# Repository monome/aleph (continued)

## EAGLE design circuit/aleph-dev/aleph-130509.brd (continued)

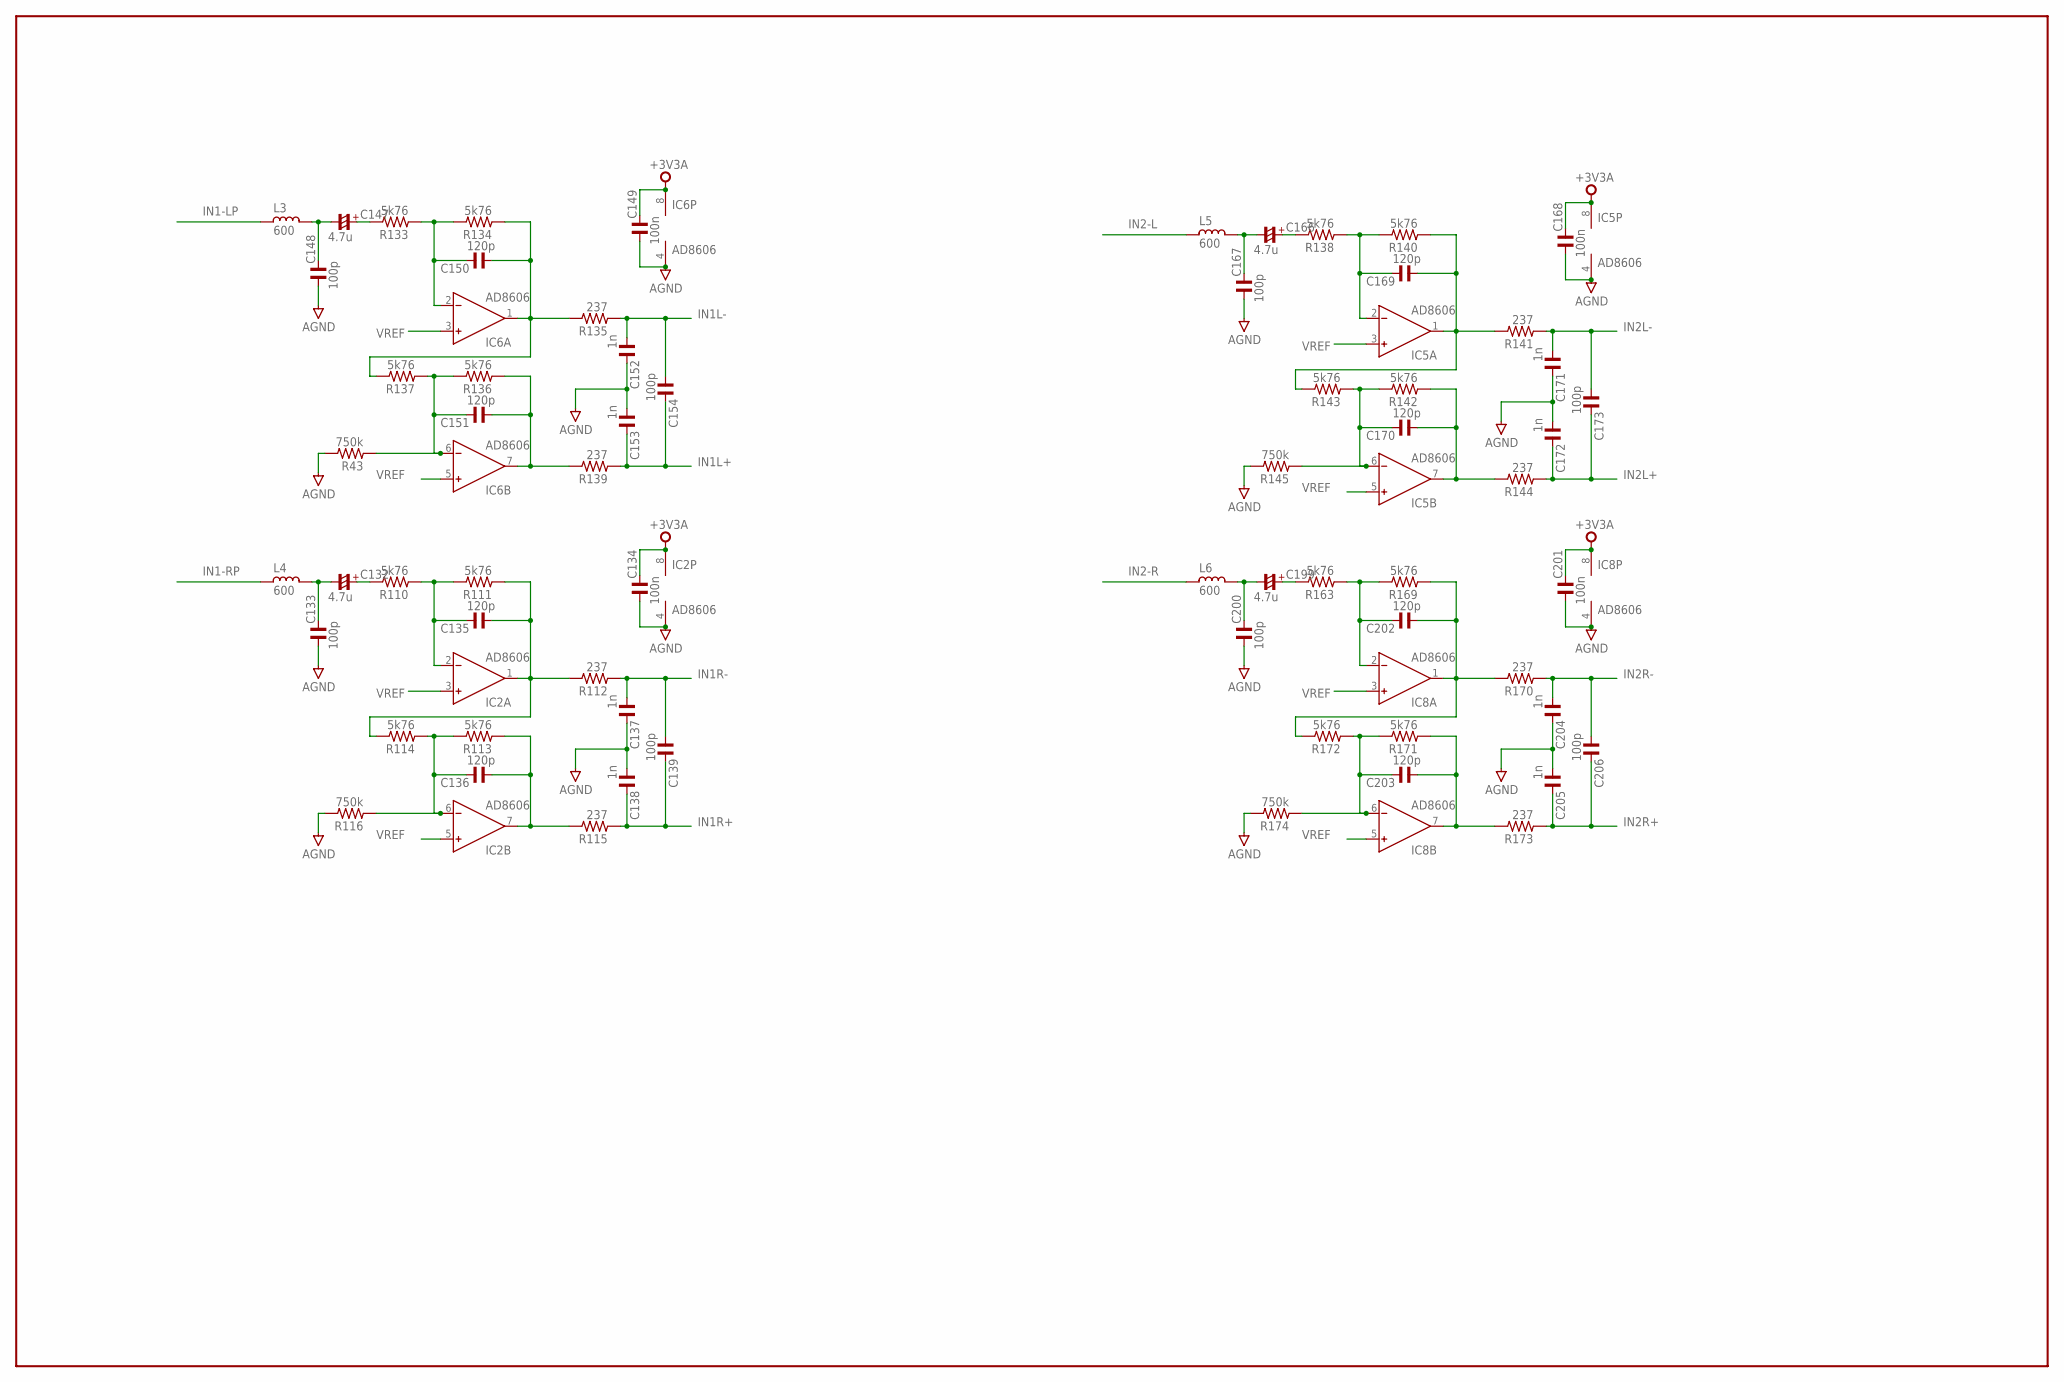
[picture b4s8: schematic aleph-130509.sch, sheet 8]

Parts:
C132, C147, C166, C199: 4.7u; C1206/T
C133, C139, C148, C154, C167, C173, C200, C206: 100p; C0603
C134, C149, C168, C201: 100n; C0603
C135, C136, C150, C151, C169, C170, C202, C203: 120p; C0603
C137, C138, C152, C153, C171, C172, C204, C205: 1n; C0603
IC2, IC5, IC6, IC8: AD8606; SO8
L3, L4, L5, L6: 600; L1206
R43, R116, R145, R174: 750k; R0603
R110, R111, R113, R114, R133, R134, R136, R137, R138, R140, R142, R143, R163, R169, R171, R172: 5k76; R0603
R112, R115, R135, R139, R141, R144, R170, R173: 237; R0603

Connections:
+3V3A: C134.2, C149.2, C168.2, C201.2, IC2.8 (V+), IC5.8 (V+), IC6.8 (V+), IC8.8 (V+); also elsewhere on the board
AGND: C133.1, C134.1, C137.2, C138.1, C148.1, C149.1, C152.2, C153.1, C167.1, C168.1, C171.2, C172.1, C200.1, C201.1, C204.2, C205.1, IC2.4 (V-), IC5.4 (V-), IC6.4 (V-), IC8.4 (V-), R43.2, R116.2, R145.2, R174.2; also elsewhere on the board
IN1-LP: L3.2; also elsewhere on the board
IN1-RP: L4.2; also elsewhere on the board
IN1L+: C153.2, C154.2, R139.1; also elsewhere on the board
IN1L-: C152.1, C154.1, R135.1; also elsewhere on the board
IN1R+: C138.2, C139.2, R115.1; also elsewhere on the board
IN1R-: C137.1, C139.1, R112.1; also elsewhere on the board
IN2-L: L5.2; also elsewhere on the board
IN2-R: L6.2; also elsewhere on the board
IN2L+: C172.2, C173.2, R144.1; also elsewhere on the board
IN2L-: C171.1, C173.1, R141.1; also elsewhere on the board
IN2R+: C205.2, C206.2, R173.1; also elsewhere on the board
IN2R-: C204.1, C206.1, R170.1; also elsewhere on the board
unnamed: C147.+, R133.2
unnamed: C135.1, IC2.1 (OUT), R111.1, R112.2, R114.2
unnamed: C136.1, IC2.7 (OUT), R113.1, R115.2
unnamed: C132.-, C133.2, L4.1
unnamed: C135.2, IC2.2 (IN-), R110.1, R111.2
unnamed: C136.2, IC2.6 (IN-), R113.2, R114.1, R116.1
unnamed: C132.+, R110.2
unnamed: C150.1, IC6.1 (OUT), R134.1, R135.2, R137.2
unnamed: C151.1, IC6.7 (OUT), R136.1, R139.2
unnamed: C147.-, C148.2, L3.1
unnamed: C150.2, IC6.2 (IN-), R133.1, R134.2
unnamed: C151.2, IC6.6 (IN-), R43.1, R136.2, R137.1
unnamed: C169.1, IC5.1 (OUT), R140.1, R141.2, R143.2
unnamed: C170.1, IC5.7 (OUT), R142.1, R144.2
unnamed: C166.-, C167.2, L5.1
unnamed: C169.2, IC5.2 (IN-), R138.1, R140.2
unnamed: C170.2, IC5.6 (IN-), R142.2, R143.1, R145.1
unnamed: C166.+, R138.2
unnamed: C202.1, IC8.1 (OUT), R169.1, R170.2, R172.2
unnamed: C203.1, IC8.7 (OUT), R171.1, R173.2
unnamed: C199.-, C200.2, L6.1
unnamed: C202.2, IC8.2 (IN-), R163.1, R169.2
unnamed: C203.2, IC8.6 (IN-), R171.2, R172.1, R174.1
unnamed: C199.+, R163.2
VREF: IC2.3 (IN+), IC2.5 (IN+), IC5.3 (IN+), IC5.5 (IN+), IC6.3 (IN+), IC6.5 (IN+), IC8.3 (IN+), IC8.5 (IN+); also elsewhere on the board

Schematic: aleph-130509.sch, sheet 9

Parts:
C196, C197, C207, C208, C210, C211: 10u; C1206/T
C198, C209: 100n; C0603
IC13, IC14: AD8607R; SO8
J13: PHA2U
LED9, LED10, LED11, LED12: LEDCHIPLED_0805; CHIPLED_0805
P7, P8: EVJ-POT
R160, R161, R166, R176, R177, R178, R179, R180, R181, R183, R184, R185: 100k; R0603
R175, R182: 50k; R0603
R186, R187: 5M; R0603

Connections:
+5VA: C198.2, C209.2, IC13.8 (V+), IC14.8 (V+); also elsewhere on the board
AGND: C198.1, C209.1, IC13.4 (V-), IC14.4 (V-), R178.1, R185.1; also elsewhere on the board
GAINL-1: IC14.6 (IN-), J13._0, R182.2
GAINL-2: C208.+, IC14.7 (OUT), R181.2, R187.2
GAINR-1: IC13.6 (IN-), J13.0, R175.2
GAINR-2: C197.+, IC13.7 (OUT), R166.2, R186.2
IN1-LP^: C211.-; also elsewhere on the board
IN1-L^: C208.-, R185.2; also elsewhere on the board
IN1-RP^: C196.-; also elsewhere on the board
IN1-R^: C197.-, R178.2; also elsewhere on the board
IN-VREF: P7.2, P7.3, P8.2, P8.3, R176.1, R177.1, R183.1, R184.1; also elsewhere on the board
unnamed: IC13.3 (IN+), R177.2
unnamed: IC13.2 (IN-), R160.2, R161.1
unnamed: C207.+, IC13.1 (OUT), R161.2
unnamed: C207.-, R175.1
unnamed: IC13.5 (IN+), R176.2
unnamed: C196.+, P8.6
unnamed: P8.1, R160.1
unnamed: IC14.3 (IN+), R184.2
unnamed: IC14.2 (IN-), R179.2, R180.1
unnamed: C210.+, IC14.1 (OUT), R180.2
unnamed: C210.-, R182.1
unnamed: IC14.5 (IN+), R183.2
unnamed: P7.1, R179.1
unnamed: C211.+, P7.6
unnamed: J13.1, R166.1
unnamed: J13.2, R186.1
unnamed: J13._1, R181.1
unnamed: J13._2, R187.1

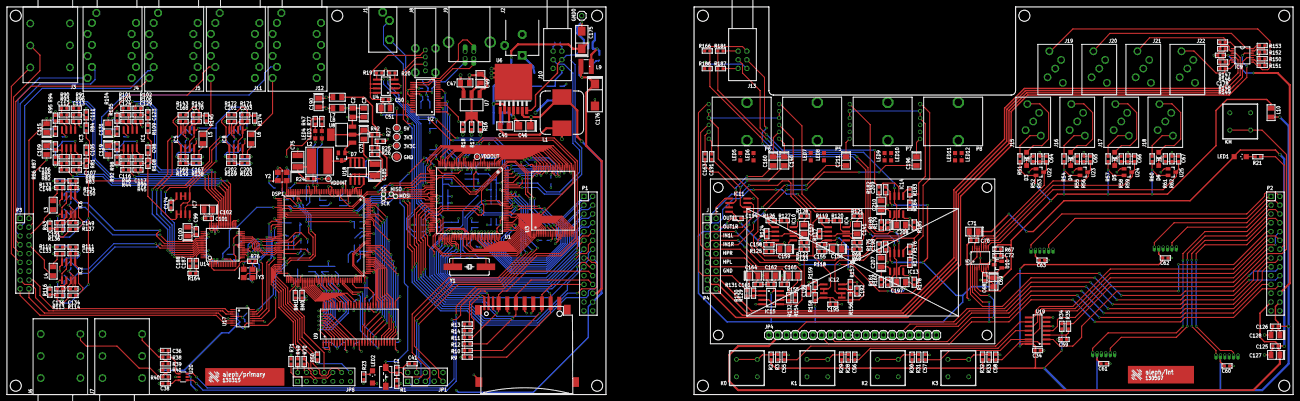
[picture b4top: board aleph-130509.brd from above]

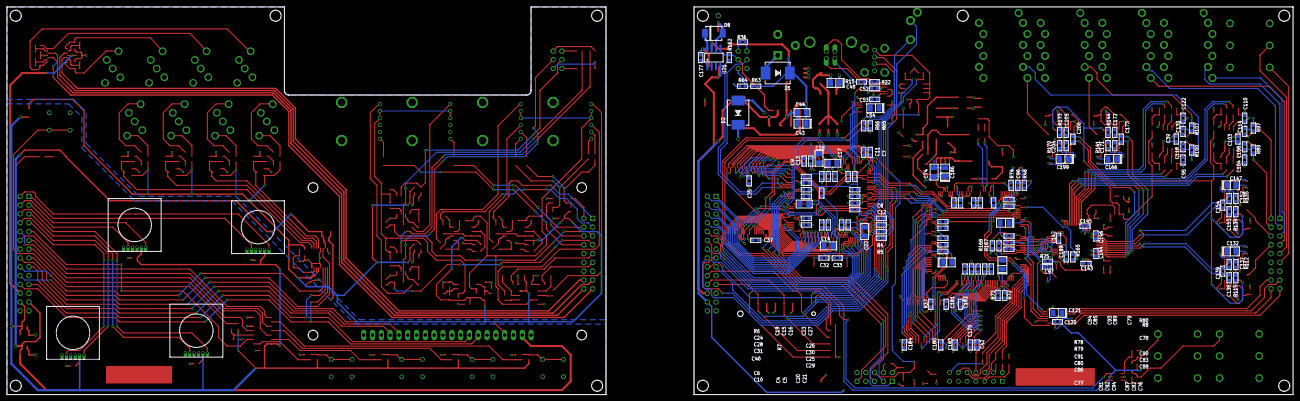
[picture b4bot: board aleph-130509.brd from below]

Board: 4 copper layers, 370.8 x 111.8 mm, 520 parts (149 on the bottom side), 424 nets.

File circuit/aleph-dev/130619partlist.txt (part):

Partlist

Exported from aleph.brd at 6/19/13 1:39 PM

EAGLE Version 6.4.0 Copyright (c) 1988-2013 CadSoft

Assembly variant: 

Part     Value              Package          Library               Position (inch)       Orientation

3V3      TPS-SMD-15R        SMD-15R          testpoint             (4.475 2.875)         R0
3V3C     TPS-SMD-15R        SMD-15R          testpoint             (4.475 2.775)         R0
5V       TPS-SMD-15R        SMD-15R          testpoint             (4.475 2.975)         R0
BM0      0                  R0603            rc-master-smd         (3.4 1.075)           R90
BM1      DNP                R0603            rc-master-smd         (3.325 1.075)         R90
C1       100n               C0603            rc-master-smd         (4.475 0.225)         R90
C2       100n               C1206            rc-master-smd         (3.975 3.15)          R270
C3       10u                C1206/T          rc-master-smd         (4.1 3.15)            R270
C4       100n               C0603            rc-master-smd         (5.4 1.875)           MR90
C5       33n                C0603            rc-master-smd         (5.325 1.875)         MR90
C6       100n               C0603            rc-master-smd         (5.575 1.95)          MR0
C7       100n               C0603            rc-master-smd         (4.85 2.7)            MR90
C8       100n               C0603            rc-master-smd         (4.725 1.95)          MR0
C9       100n               C0603            rc-master-smd         (5.6 2.6)             MR90
C10      33n                C0603            rc-master-smd         (5.575 1.875)         MR0
C11      33n                C0603            rc-master-smd         (4.925 2.7)           MR90
C12      33n                C0603            rc-master-smd         (4.725 1.875)         MR0
C13      33n                C0603            rc-master-smd         (5.525 2.6)           MR90
C14      4.7u               C1206            rc-master-smd         (5.325 1.6375)        MR180
C15      33n                C0603            rc-master-smd         (5.325 2.425)         MR270
C16      100n               C0603            rc-master-smd         (5.25 2.425)          MR270
C17      4.7u               C1206            rc-master-smd         (5.275 2.575)         MR0
C18      2.2u               C1206            rc-master-smd         (5.43125 2.63125)     MR90
C19      470p               C0603            rc-master-smd         (5.4 2.425)           MR270
C20      2.7n               C0603            rc-master-smd         (5.175 1.875)         MR90
C21      33n                C0603            rc-master-smd         (5.1 1.875)           MR90
C22      2.2u               C1206            rc-master-smd         (4.9125 1.8)          MR90
C23      2.7n               C0603            rc-master-smd         (5.1 2.425)           MR270
C24      2.7n               C0603            rc-master-smd         (5.575 2.35)          MR0
C25      2.7n               C0603            rc-master-smd         (5.025 2.125)         MR180
C26      2.7n               C0603            rc-master-smd         (5.025 2.275)         MR180
C27      33n                C0603            rc-master-smd         (5.025 2.425)         MR270
C28      33n                C0603            rc-master-smd         (5.575 2.275)         MR0
C29      33n                C0603            rc-master-smd         (5.025 2.05)          MR180
C30      33n                C0603            rc-master-smd         (5.025 2.2)           MR180
C31      100n               C0603            rc-master-smd         (5.575 2.2)           MR0
C32      18p                C0603            rc-master-smd         (5.375 1.5)           MR0
C33      18p                C0603            rc-master-smd         (5.225 1.5)           MR180
C34      100n               C0603            rc-master-smd         (11.75 0.45)          R180
C35      10n                C0603            rc-master-smd         (6.225 2.375)         MR270
C36      1u                 C0603            rc-master-smd         (1.85 0.45)           R0
C37      10n                C0603            rc-master-smd         (6.15 1.7)            MR0
C38      1u                 C0603            rc-master-smd         (1.85 0.075)          R0
C39      100n               C0603            rc-master-smd         (1.375 2.85)          MR90
C40      2.2u               C1206            rc-master-smd         (5.6 2.1125)          MR0
C41      100n               C0603            rc-master-smd         (4.65 0.3)            R180
C42      10n                C0603            rc-master-smd         (3.6375 0.5125)       MR270
C43      22u                C1206/T          rc-master-smd         (5.625 3.025)         MR0
C44      470n               C1206            rc-master-smd         (5.625 3.15)          MR0
C45      10n                C1206            rc-master-smd         (5.7 3)               R0
C46      47u                C3528/T          rc-master-smd         (5.925 3)             R0
C47      100n               C1206            rc-master-smd         (5.25 3.4875)         R180
C48      10u                C1206/T          rc-master-smd         (5.25 3.4875)         MR0
C49      10u                C1206/T          rc-master-smd         (5.425 3.5375)        R270
C50      100n               C0603            rc-master-smd         (4.35 3.3)            R180
C51      4.7u               C1206/T          rc-master-smd         (4.35 3.2)            R180
C52      100n               C0603            rc-master-smd         (4.8 3.425)           MR0
C53      100n               C0603            rc-master-smd         (4.8 3.3)             MR0
C54      4.7u               C1206/T          rc-master-smd         (4.8 3.2)             MR0
C55      1u                 C0603            rc-master-smd         (8.875 0.375)         R270
C56      1u                 C0603            rc-master-smd         (9.675 0.375)         R270
C57      1u                 C0603            rc-master-smd         (10.475 0.375)        R270
C58      1u                 C0603            rc-master-smd         (11.275 0.375)        R270
C59      1u                 C0603            rc-master-smd         (12.05 0.575)         R0
C60      100n               C0603            rc-master-smd         (13.9 0.275)          R180
C61      100n               C0603            rc-master-smd         (12.5 0.3)            R180
C62      100n               C0603            rc-master-smd         (13.2 1.5)            R180
C63      100n               C0603            rc-master-smd         (11.8 1.475)          R180
C64      10n                C0603            rc-master-smd         (11.85 2.625)         R90
C65      10n                C0603            rc-master-smd         (12.35 2.625)         R90
C66      10n                C0603            rc-master-smd         (12.85 2.625)         R90
C67      10n                C0603            rc-master-smd         (13.35 2.625)         R90
C68      100n               C0603            rc-master-smd         (11.15 1.275)         R90
C69      10u                C1206/T          rc-master-smd         (11.25 1.225)         R90
C70      100n               C0603            rc-master-smd         (11.025 1.7)          R0
C71      10u                C1206/T          rc-master-smd         (11.025 1.8)          R0
C72      100n               C0603            rc-master-smd         (11.3 1.525)          R0
C73      10u                C1206/T          rc-master-smd         (4.1 2.9)             R90
C74      100n               C1206            rc-master-smd         (4.125 2.475)         MR270
C75      100u               C1210/T          rc-master-smd         (3.35 2.6)            R270
C76      10u                C1206/T          rc-master-smd         (3.35 1.425)          MR270
C77      10u                C1206/T          rc-master-smd         (3.975 1.45)          MR180
C78      10u                C1206/T          rc-master-smd         (3.325 1.9)           MR0
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
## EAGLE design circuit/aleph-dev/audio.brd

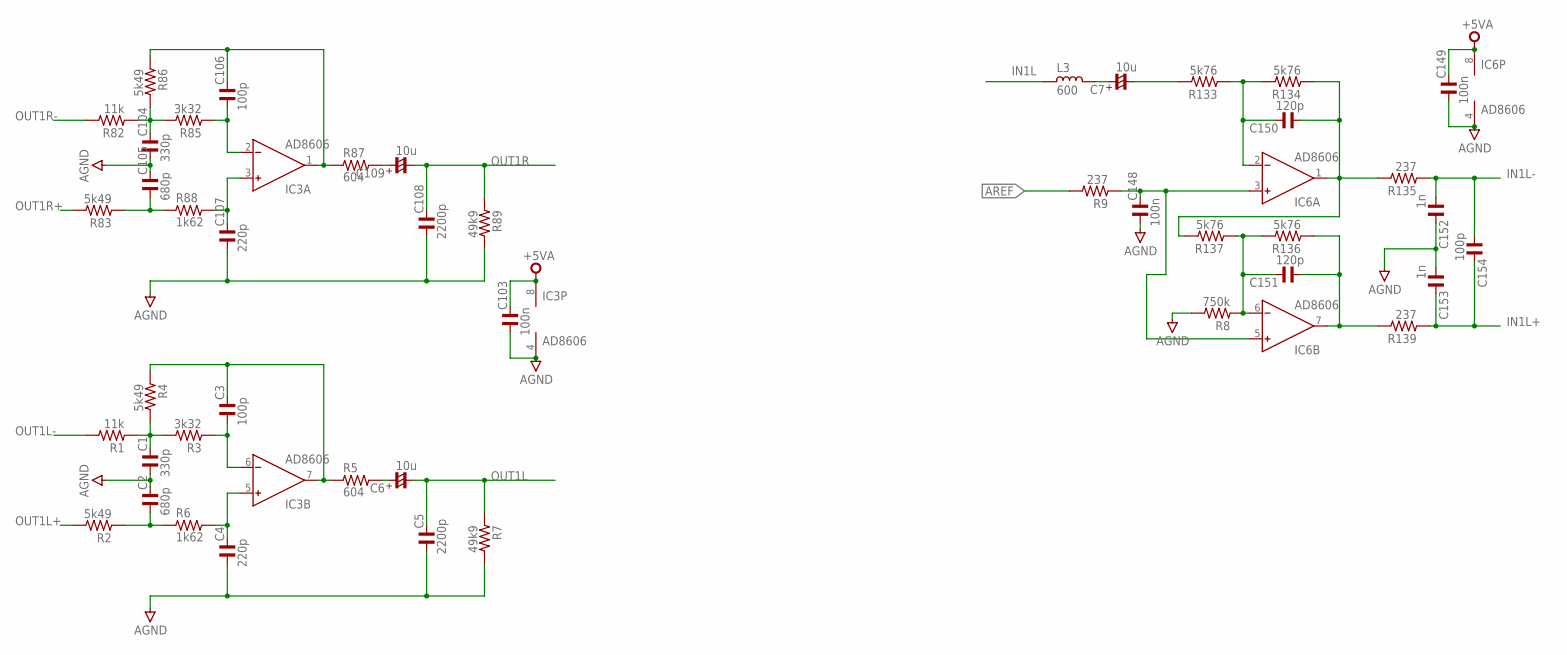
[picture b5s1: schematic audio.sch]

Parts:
C1, C104: 330p; C0603
C2, C105: 680p; C0603
C3, C106, C154: 100p; C0603
C4, C107: 220p; C0603
C5, C108: 2200p; C0603
C6, C7, C109: 10u; C1206/T
C103, C148, C149: 100n; C0603
C150, C151: 120p; C0603
C152, C153: 1n; C0603
IC3, IC6: AD8606; SO8
L3: 600; L1206
R1, R82: 11k; R0603
R2, R4, R83, R86: 5k49; R0603
R3, R85: 3k32; R0603
R5, R87: 604; R0603
R6, R88: 1k62; R0603
R7, R89: 49k9; R0603
R8: 750k; R0603
R9, R135, R139: 237; R0603
R133, R134, R136, R137: 5k76; R0603

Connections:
+5VA: C103.2, C149.2, IC3.8 (V+), IC6.8 (V+)
AGND: C1.1, C2.2, C4.1, C5.1, C103.1, C104.1, C105.2, C107.1, C108.1, C148.1, C149.1, C152.2, C153.1, IC3.4 (V-), IC6.4 (V-), R7.2, R8.2, R89.2
AREF: R9.2
IN1L: L3.2
IN1L+: C153.2, C154.2, R139.1
IN1L-: C152.1, C154.1, R135.1
unnamed: C1.2, R1.1, R3.2, R4.2
unnamed: C2.1, R2.1, R6.1
unnamed: C4.2, IC3.5 (IN+), R6.2
unnamed: C3.2, IC3.7 (OUT), R4.1, R5.1
unnamed: C6.+, R5.2
unnamed: C3.1, IC3.6 (IN-), R3.1
unnamed: C7.+, L3.1
unnamed: C7.-, R133.2
unnamed: C148.2, IC6.3 (IN+), IC6.5 (IN+), R9.1
unnamed: C104.2, R82.1, R85.2, R86.2
unnamed: C105.1, R83.1, R88.1
unnamed: C107.2, IC3.3 (IN+), R88.2
unnamed: C106.2, IC3.1 (OUT), R86.1, R87.1
unnamed: C109.+, R87.2
unnamed: C106.1, IC3.2 (IN-), R85.1
unnamed: C150.1, IC6.1 (OUT), R134.1, R135.2, R137.2
unnamed: C151.1, IC6.7 (OUT), R136.1, R139.2
unnamed: C150.2, IC6.2 (IN-), R133.1, R134.2
unnamed: C151.2, IC6.6 (IN-), R8.1, R136.2, R137.1
OUT1L: C5.2, C6.-, R7.1
OUT1L+: R2.2
OUT1L-: R1.2
OUT1R: C108.2, C109.-, R89.1
OUT1R+: R83.2
OUT1R-: R82.2

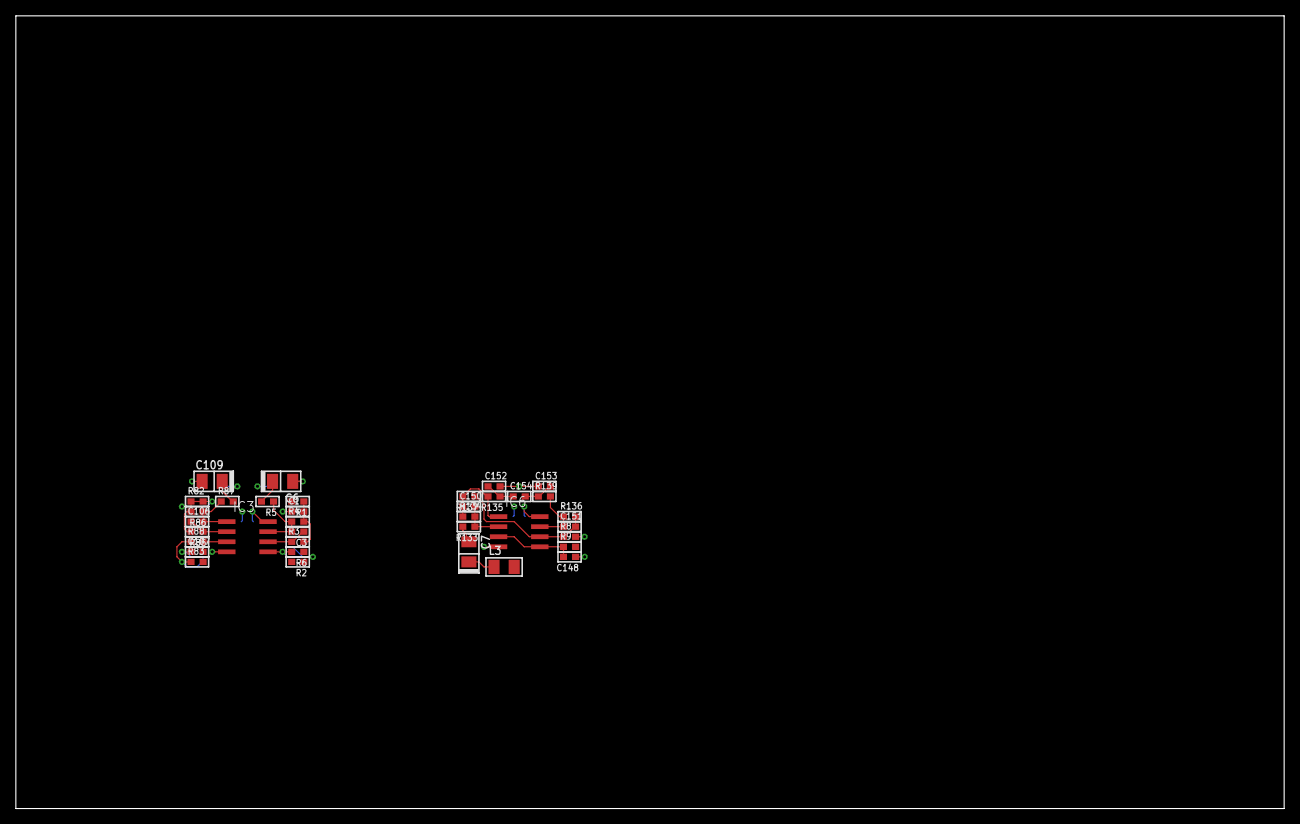
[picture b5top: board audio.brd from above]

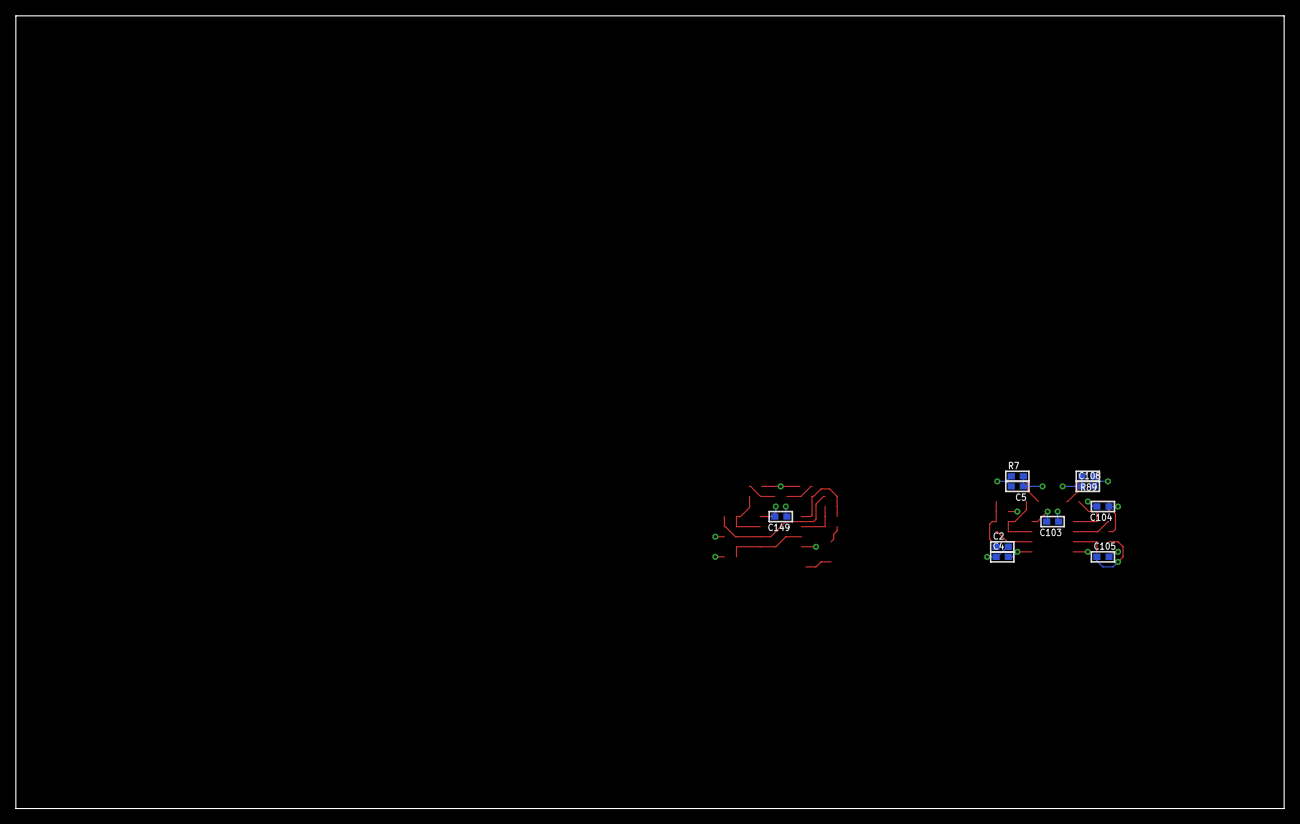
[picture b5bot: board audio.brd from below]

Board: 2 copper layers, 160.0 x 100.0 mm, 46 parts (10 on the bottom side), 25 nets.

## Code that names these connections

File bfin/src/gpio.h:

#ifndef _ALEPH_BFIN_GPIO_H_
#define _ALEPH_BFIN_GPIO_H_

// codec reset
#define CODEC_RESET_PIN	   1
#define CODEC_RESET_UNMASK (1 << CODEC_RESET_PIN)
#define CODEC_RESET_MASK   (0xffff ^ CODEC_RESET_UNMASK)
#define CODEC_RESET_LO	   *pFIO_FLAG_D &= CODEC_RESET_MASK
#define CODEC_RESET_HI     *pFIO_FLAG_D |= CODEC_RESET_UNMASK

// dac reset 
#define DAC_RESET_PIN	 6
#define DAC_RESET_UNMASK (1 << DAC_RESET_PIN)
#define DAC_RESET_MASK   (0xffff ^ DAC_RESET_UNMASK)
#define DAC_RESET_LO	 *pFIO_FLAG_D &= DAC_RESET_MASK
#define DAC_RESET_HI  	 *pFIO_FLAG_D |= DAC_RESET_UNMASK

// "ready" pin - pf12
// set high when able to receive param changes
// e.g. init finished, frame finished
#define READY_PIN        12
#define READY_UNMASK 	(1 << READY_PIN)
#define READY_MASK	(0xffff ^ READY_UNMASK)
#define READY_LO 	*pFIO_FLAG_D &= READY_MASK
#define READY_HI 	*pFIO_FLAG_D |= READY_UNMASK

// "request" pin - pf13
// should it prove necessary, bfin will use this pin
// to trigger interrupts on avr32.
#define REQUEST_PIN        13
#define REQUEST_UNMASK 	(1 << REQUEST_PIN)
#define REQUEST_MASK	(0xffff ^ REQUEST_UNMASK)
#define REQUEST_LO 	*pFIO_FLAG_D &= REQUEST_MASK
#define REQUEST_HI 	*pFIO_FLAG_D |= REQUEST_UNMASK

// leds are on pf14, pf15
#define LED3_PIN 	14
#define LED3_UNMASK     (1 << LED3_PIN)
#define LED3_MASK       (0xffff ^ LED3_UNMASK)
#define LED3_LO		*pFIO_FLAG_D &= LED3_MASK
#define LED3_HI 	*pFIO_FLAG_D |= LED3_UNMASK
#define LED3_TOGGLE	*pFIO_FLAG_D ^= LED3_UNMASK

#define LED4_PIN 	15
#define LED4_UNMASK     (1 << LED4_PIN)
#define LED4_MASK       (0xffff ^ LED4_UNMASK)
#define LED4_LO		*pFIO_FLAG_D &= LED4_MASK
#define LED4_HI 	*pFIO_FLAG_D |= LED4_UNMASK
#define LED4_TOGGLE	*pFIO_FLAG_D ^= LED4_UNMASK


#endif // h guard

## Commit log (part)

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2017-05-08 print op_sizes on beekeep boot, don't explode
2017-05-08 squash multiple definition of SCALES
2017-05-08 add op_poly to BEES (note priority selection)
2017-05-08 wasteful inline declarations in kria
2017-05-08 make bees_op external threadsafe
2017-05-08 add picolisp app (encoders + screen only)
2017-05-08 remove unused variables in kria
2017-05-08 decruft pd, timing correct bees execution time
2017-05-08 grid raw pickle LEDs
2017-05-10 improve alt key accelerator for out target select
2017-05-10 disable the 'meat' of kria op in debug build
2017-05-10 set monome & midi poll timers to 5ms
2017-05-10 handle connected monome correctly on boot
2017-05-11 16 bit audio buffers & debug 'tape' module
2017-05-11 don't use pointer to void unnecessarily in dsyn
2017-05-11 make delayFadeN 16 bit
2017-05-11 make all lines' mixing 16 bit
2017-05-11 make lines use 24_8 everywhere
2017-05-11 debug test for lines varispeed read heads
2017-05-11 lines with vari-speed read/write
2017-05-12 add bfin PD external (hardwired to fmsynth)
2017-05-12 add bfin test scene
2017-05-12 add a banger to fmsynth
2017-05-12 (roughly) hack param scaler code into bfin_pd
2017-05-12 probe more of the param scaler code
2017-05-12 better param indexing/description
2017-05-12 split makefile up to enable build other modules
2017-05-12 fixup makefile for pd lines
2017-05-12 make write head run backwards
2017-05-12 attempt to handle preLevel properly
2017-05-13 fixing 24_8 interpolating buffers
2017-05-13 fixing lines
2017-05-13 optimise fwd interp write some more
2017-05-13 limit interpolated writes to forwards
2017-05-13 use circptrs in interp write algorithm
2017-05-13 hacking towards optimised version
2017-05-13 non-mixing version of reverse interp slow writes
2017-05-13 slow, reverse interp additive writes
2017-05-13 fixup
2017-05-13 reuse conditional from reverse slow interp on fwd
2017-05-13 linear fwd/backward _add & _mix writes
2017-05-14 add 16 bit bspline interpolation algorithm
2017-05-14 add bspline interpolated reads to buffer16.c
2017-05-16 make delayFade24_8 use the bspline read
2017-05-21 duplicate dsyn into new acid module
2017-05-21 make filter_2p work with make sim target
2017-05-21 clean up arch_linux declarations in acid.c
2017-05-21 de-cruft dsyn noise generation
2017-05-21 tell osc params on cmd line in sim
2017-05-21 clean up acid noise/svf/amp routing
2017-05-21 saner naming for 16 bit adsr envs
2017-05-21 'auto-off' adsr envs (aka trigger adsr)
2017-05-21 fix segfault, re-index params etc
2017-05-21 hack sensible defaults into acid dsyn
2017-05-22 correction to header guard naming
2017-05-22 303-ish object
2017-05-22 fix param desc build for new acid module
2017-05-22 plumb monosynth module in to acid sound output
2017-05-22 fix monosynth param descriptor in acid module
2017-05-22 add noise reset to dsyn_voice, clean it's struct
2017-05-23 add 12dB hard clipping to dsyn voice pre & post
2017-05-23 add tweakable params to bassline synth
2017-05-24 increase number of voices, fix bugs
2017-05-24 add filterType switch to monosynth filter
2017-05-27 pickle kria scales to scene
2017-06-04 fix bug where preset param exclude doesn't save
2017-06-04 fix preset reshuffling on op deletion
2017-09-18 fix kria alt key behaviour?
2017-10-02 looks like a reported bug in op_mul
2017-10-02 wrapper to compile BEES as pd external
2017-10-02 improved monome grid focus functionality
2017-10-02 fix bug in avr32lib software timers
2017-10-02 pickling state for op_step
2017-10-02 correct alphabetic order for op_param
2017-10-24 don't bang op_enc outputs when changing it's input
2017-10-24 fix routing/mixing bug in fmsynth module
2017-10-29 add blackfin build doc on macOS with Docker
2017-10-30 add oversampling feature to fmsynth module
2017-10-30 made oversampling FM use 16 bit throughout
2017-10-30 seemingly working oversampled fm
2017-10-30 add waveshape control to fmsynth
2017-11-02 update displayed value of enc op when val updated
2017-11-02 add aleph-specific avr32 boilerplate sources in avr32/
2017-11-02 remove old avr32_lib/
2017-11-02 fix sources in common/
2017-11-02 add font sources
2017-11-02 fix bees sources and makefiles
2017-11-02 bump bees revision
2017-11-02 fix low-level blank avr32 app template
2017-11-02 add clang-format
2017-11-02 add libavr32 as submodule
2017-11-02 very minor README update
2017-11-02 add linker script and startup ASM
2017-11-02 change .gitmodules to point at upstream libavr32
2017-11-02 fix up my changes against new avr32lib
2017-11-03 changes to libavr32 to fix BEES
2017-11-05 refactor fmsynth to use 32 bit envs
2017-11-05 get rid of oscillator waveshape
2017-11-05 make bandlimit a param, fix DSP bug
2017-11-05 add external modulator control to fmsynth
2017-11-06 allow 4x overdrive of clipping FM
2017-11-06 tweak antialias filter & mod saturation
2017-11-06 added per-voice bandlimit, saturate, portamento
2017-11-06 resurrect ladder filter from an old branch
2017-11-06 don't upsample volume envs
2017-11-06 clean non-oversampled envs a bit
2017-11-06 remove redundant ext modulator interpolation
2017-11-06 initialise connected monome grid correctly on boot
2017-11-06 fix make tags after libavr32 merge
2017-11-06 reinsert BEES' serial protocol with libavr32
2017-11-07 BEES code outside header guard
2017-11-07 shuffle start/pause timers song/dance into BEES
2017-11-07 fix pd BEES external compilation
2017-11-07 fix preset reshuffling on op insertion/deletion
2017-11-07 hack to fix focus-stealing on scene recall
2017-11-07 fix edgecase in white whale seriesMode/choice
2017-11-07 fix bounds checking on op_mem1d & op_mem2d
2017-11-07 fix up acid after correction to adsr env slews
2017-11-08 initialise 16x8 grid cleanly in op_step
2017-11-08 pickle ledBuffers in op_step
2017-11-08 resurrect 'old lines' from 1c7d00b0a86920fdef5b83dd54a042a5bbd47414
2017-11-08 improve op_random
2017-11-08 add midi program change operator
2017-11-09 add missing linker script for varilines
2017-11-09 rm pitchtoy from the work tree till it's fixed
2017-11-09 first attempt at midi_common merge
2017-11-10 fixup midi ops after merging with midi_common
2017-11-10 added program change messages to midi_common
2017-11-10 crank poll timers back down to very slow
2017-11-10 successful first contact for usb midi output!
2017-11-10 bad hack: add WDT driver sources from ASF
2017-11-10 minor cleanup of dead code
2017-11-10 re-disable wdt at top of main
2017-11-10 remove old avr32_test
2017-11-14 rename dummyLedBuffer to defaultLedBuffer
2017-11-14 nuke liferaw to claw back space
2017-11-14 update libavr32 submodule to point at monome/libavr32
2017-11-15 squash warnings with different optimisation level
2017-11-15 optimise BEES for code size
2017-11-15 add cable number to midi_out_cc
2017-11-15 add midi clock out, deinit midiprog & midiclk
2017-11-15 switch to optimisation -O2 (same code size as -Os)
2017-11-15 rebase libavr32 midi changes a bit
2017-11-16 fix midi_clk ops (zero ins/outs explode on deinit)
2017-11-16 shorten midi labels for out screen readability
2017-11-16 libavr32 submodule update
2017-11-17 fix beekeep & BEES pd external
2017-11-17 reshuffle new midi_clk op into life_raw op slot
2017-11-17 add prog input & dummy output to midi_note_out
2017-11-17 fix cv output (ad5686) by disabling DMA4 autobuffer
    also clean a lot of dead code from bfin_lib
2017-11-18 remove slew 'sync' from lines, varilines, waves
2017-11-20 README to build the PD external
2017-12-14 make 2ms the timebase for lines' time quantities
2017-12-14 initialise *all* lines' params on boot
2017-12-14 initialise loops & delays in correct radix
2017-12-14 convert DELAY to same time units LINES/METRO/TIMER
2017-12-15 add metro subdivision feature
2017-12-15 cache division/remainder operations
2017-12-15 pickle/unpickle divide METRO divide param
2017-12-15 revert op_metro to break less scene compat.
2017-12-15 add linlin operator
2017-12-15 change 'STATE' to 'BANG' in op_tog
2017-12-15 tidy up linlin, ensure correct rounding
2017-12-15 make ckdiv reset correctly on ENABLE or PERIOD
2017-12-15 cleanup BEES timing-op changes
2017-12-15 change BEES/lines clocks back to 1ms
2017-12-16 add timescale param to lines
2017-12-16 make some notes on param radix convention
2017-12-16 add to param_fettling instructions
2017-12-16 remove 1ms/2ms confusion in function names
2017-12-16 correction to #define NUM_USER_OP_TYPES
2017-12-17 relax cautionary div/mul fade checks
2017-12-17 pilfer normalising lowpass from CV-fix branch
2017-12-18 strip down lines params, add some slews
2017-12-18 revert new cpu-hogging slews
2017-12-18 typo in param_set for wet1slew
2017-12-18 wet/dry mix slews (dacs 1,2,3 disabled for test)
2017-12-18 use 'lines classic' slews on wet/dry slews
2017-12-18 move all mixing over to 16 bit processing
2017-12-18 improve lines' filter ramp implementation
2017-12-18 equal-power crossfades in lines
2017-12-18 comment out sync logic & remove unused fn
2017-12-18 add back in a param for mix slew
2017-12-18 correction to globalTimescale radix
2017-12-18 change LINLIN to LL on INS/OUTS pages
2017-12-18 use non-normalising slews to save cpu
2017-12-18 restore slew sync, relax sync threshold to ~102dB
2017-12-18 simplify buffer.c
2017-12-18 don't use trivial setter functions
2017-12-18 revert to linear xfade
2017-12-18 squash all compile warnings
2017-12-19 remove slew syncs once & for all
2017-12-19 explicit typecast when using memset
2017-12-19 remove rq slew & dry slew
2017-12-19 zero outputs in mix_outputs
2017-12-19 handle globalTimescale routing a bit differently
2017-12-19 Revert "remove rq slew & dry slew"
    This reverts commit 22098a8f97528ac28f001ea738b07ebed2e32c63.
2017-12-19 add dummy param, shuffle timescale to back
2017-12-19 allow max 1 bfin param per ms
2017-12-20 fade-in/fade-out for write head
2017-12-20 add list4 operator to BEES
2017-12-20 add LINLIN to BEES docs
2017-12-20 update op documentation for MIDI ops
2017-12-20 update docs for history, add proposed ops to doc
2017-12-20 import oplist document from word doc as markdown
2017-12-20 add CKDIV to BEES docs
2017-12-20 actually remember to check in list4
2017-12-20 add stub inputs for WW cut & pattern controls
2017-12-20 add dummy outputs to all zero-output BEES ops
2017-12-20 add address / data output stubs to serial op
2017-12-20 update BEES doc to include future-feature stubs
2017-12-20 add dummy param to waves descriptor
2017-12-20 add dummy param to grains descriptor
2017-12-20 correction to SLEW constants in ricks_tricks
2017-12-21 revert CV driver change ecf1b324
2017-12-21 Revert "add dummy param to fmsynth descriptor"
    This reverts commit 874fa6f0989eb3c87c758079658b70f8507b0f55.
2017-12-21 Revert "add dummy param to waves descriptor"
    This reverts commit b87199e0cbcfa60d827a054d9150dda7bff05615.
2017-12-21 Revert "add dummy param to grains descriptor"
    This reverts commit 8243950d9112fe62caca414825241fa99d483187.
2017-12-21 add new modules to install.sh
2017-12-21 Revert "fade-in/fade-out for write head"
    This reverts commit f95ccd6f36218f63e319a5d396c14bfa9a4c5880.
2017-12-21 bump BEES version number to 0.8.0
2017-12-21 bump lines version 0.2.5
2017-12-21 bump waves version number
2017-12-21 bump fmsynth version number
2017-12-21 bump acid version number
2017-12-23 improve freq_to_phase calculation
2017-12-23 bring up same frequencies on boot
2017-12-25 better bounds checking for hz-scaler linear interp
2017-12-25 print 256-per-semitone microtuning on INS page
2017-12-25 bug in linlin unpickling
2017-12-25 DACS3/4 mirror main stereo outs on fmsynth
2018-01-17 bump bees version number
2018-01-17 remove half-baked modules from install script
2018-01-17 bump modules affected by freq/tune
2018-01-18 restore op_random state correctly after unpickle
2018-01-23 Update config.mk
    Added HIST2 and ROUTE2
2018-01-23 Added Hist2 and Route2
2018-01-23 Added Route2 and Hist2
2018-01-24 Revert "prgm sample transfer"
2018-04-15 Update op.c
    corrected line 73, coma missing
2018-04-15 Update op.c
    Coma missing in line 73 - corrected
